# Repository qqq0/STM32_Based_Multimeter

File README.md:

# **STM32 BLE Multimeter**

**Multimeter features:**
- USB rechargeable LiPo battery  
- BLE control and data streaming  
- Auto range detection  
- Optional OLED display/button control  

**Measurement types:**
- DC voltage: 0 - 60V  
- DC current: 0 - 10A (5 sec)  
- DC power: 0 - 600 W (5 sec)  
- Resistance: 1 - 1M ohm  
- Inductance  
- Capacitance (non-polarized)  
- Diode: 3.3V  

**PCB FRONT:**

**PCB BACK:**

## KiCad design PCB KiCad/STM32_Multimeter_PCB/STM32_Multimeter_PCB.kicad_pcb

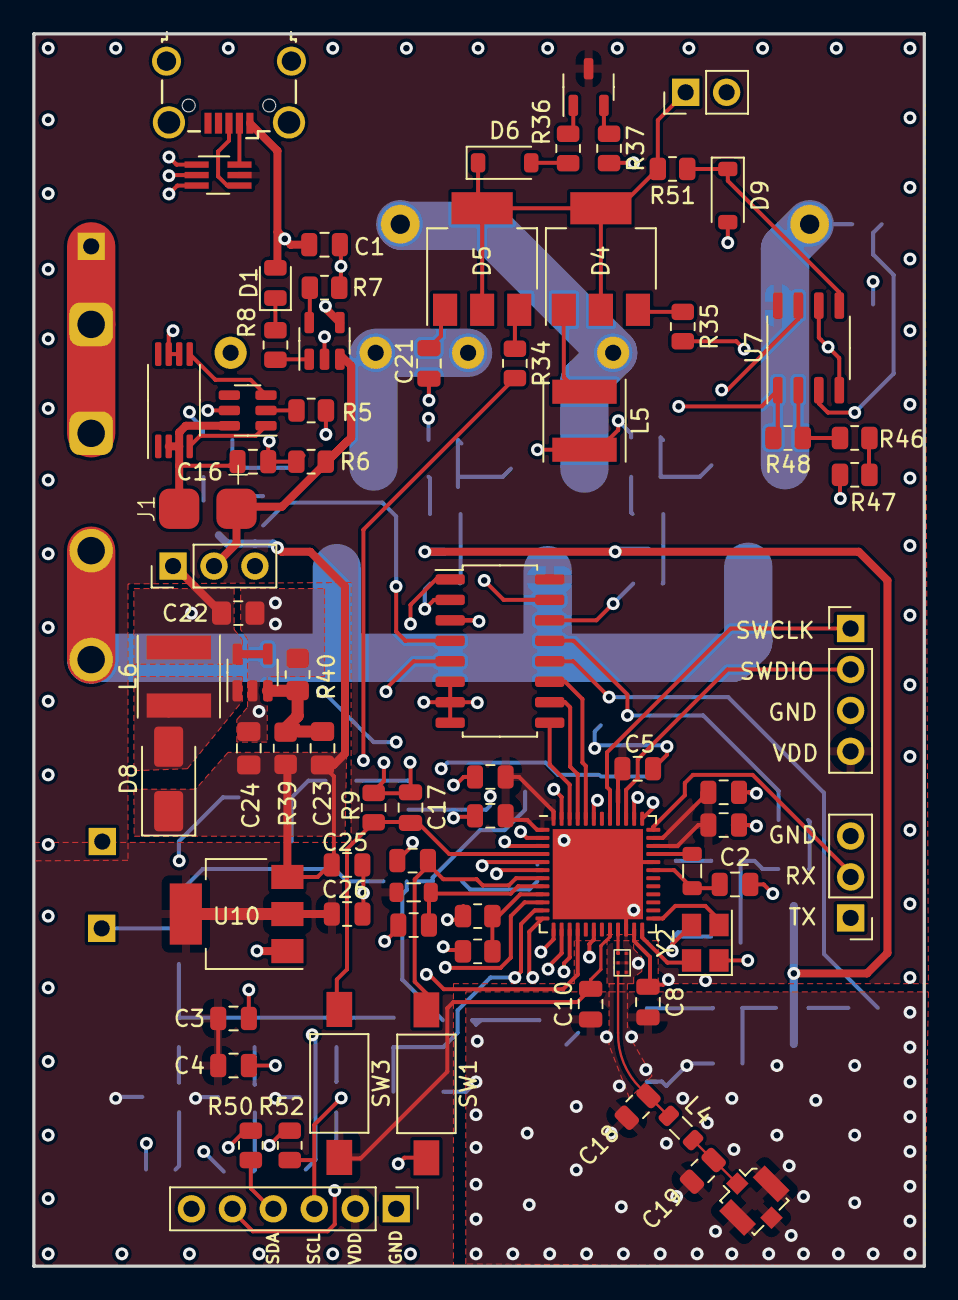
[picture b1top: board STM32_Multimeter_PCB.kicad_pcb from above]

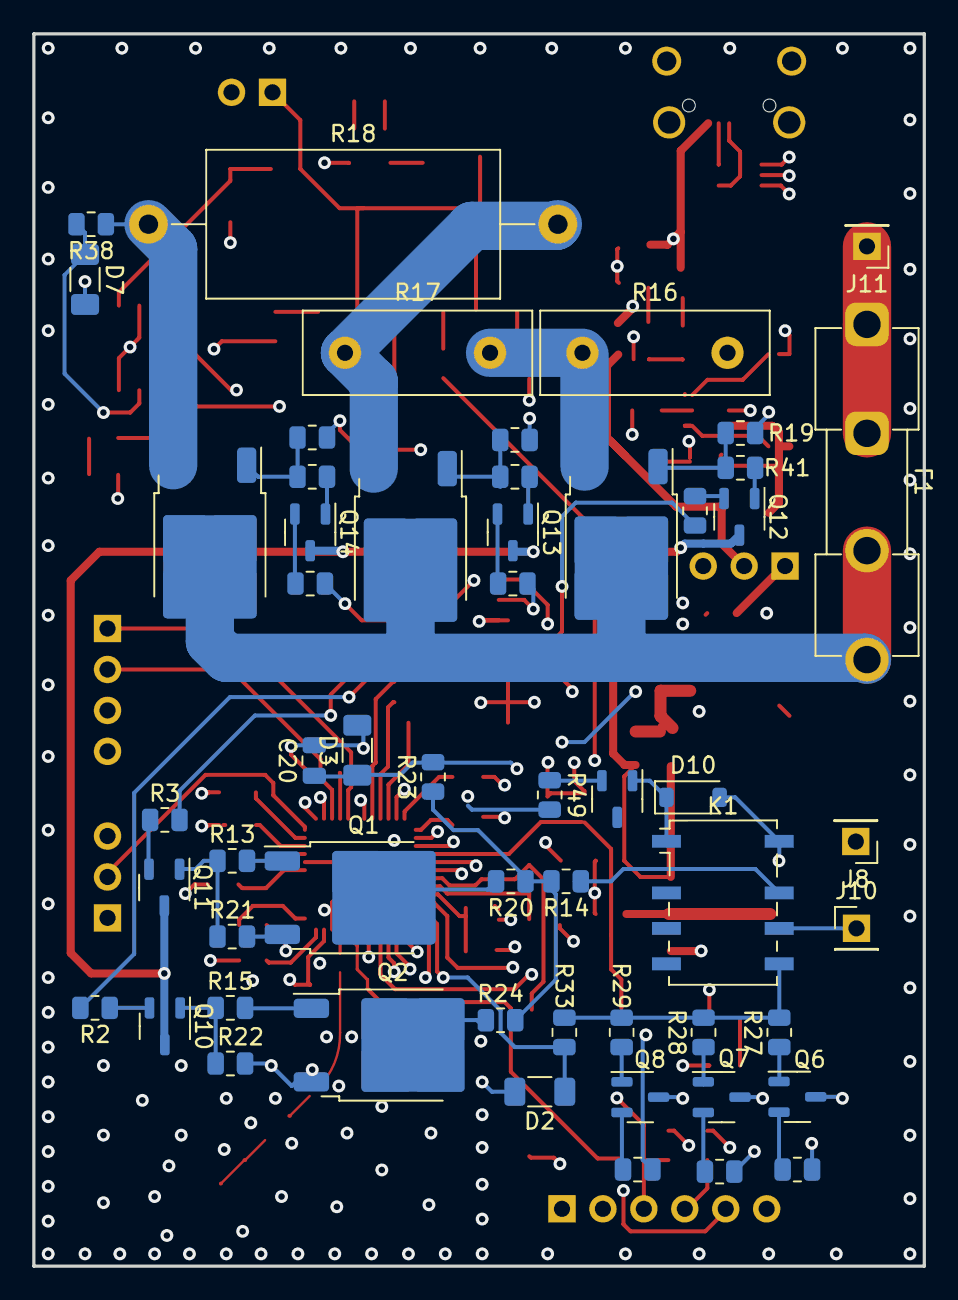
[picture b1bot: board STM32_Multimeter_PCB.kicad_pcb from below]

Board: 4 copper layers, 55.2 x 76.5 mm, 130 parts (55 on the bottom side), 105 nets.

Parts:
C1, C2, C3, C4, C11: 4,7 uF; C_0805_2012Metric
C5, C6, C7, C8, C9, C10, C12, C13, C16, C17, C20: 100 nF; C_0805_2012Metric
C18, C19: NF; C_0805_2012Metric
C21: 1uF; C_0805_2012Metric
C22, C24: 4.7uF; C_0805_2012Metric_Pad1.18x1.45mm_HandSolder
C23: 22pF; C_0805_2012Metric_Pad1.18x1.45mm_HandSolder
C25, C26: 10 uF; C_0805_2012Metric
D1: LED; LED_0805_2012Metric
D2, D3, D7: 3V3 D_Zener; R_1206_3216Metric_Pad1.30x1.75mm_HandSolder
D4, D5: Z0103MN; SOT-223
D6, D9, D10: 1N4148W; D_SOD-123
D8: 1N4001; D_SMA
F1: 10A Fuse; Fuseholder_Clip-5x20mm_Eaton_1A5601-01_Inline_P20.80x6.76mm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
J1: Conn_01x02_Pin; batt
J2: USB_B_Micro; USB_Micro-B_Wuerth_629105150521_CircularHoles
J3: Conn_01x04_Pin; PinHeader_1x04_P2.54mm_Vertical
J4: Conn_Coaxial; U.FL_Molex_MCRF_73412-0110_Vertical
J5: Conn_01x03_Pin; PinHeader_1x03_P2.54mm_Vertical
J7: Conn_01x02_Pin; PinHeader_1x02_P2.54mm_Vertical
J8, J10, J11: Conn_01x01_Pin; PinHeader_1x01_P2.54mm_Vertical
J9: Conn_01x06_Pin; PinHeader_1x06_P2.54mm_Vertical
K1: G6K-2; Relay_DPDT_Omron_G6K-2F-Y
L1, L2: 10 uH; L_0805_2012Metric
L4: 0H; L_0805_2012Metric
L5, L6: 10uH; L_Taiyo-Yuden_NR-50xx
Q1, Q2, Q3, Q4, Q5: AOD2810; TO-252-1
Q6, Q7, Q8, Q9, Q10, Q11, Q12, Q13, Q14, Q15: BC327; SOT-23-3
R2, R3, R4, R30, R31, R32, R34, R35, R37, R43, R45, R49: 2k2 R; R_0805_2012Metric
R5, R8, R13, R15, R28, R41, R42, R44: 1k R; R_0805_2012Metric
R6: 100R; R_0805_2012Metric
R7, R9, R50, R52: 2k R; R_0805_2012Metric
R11, R12: 511k R; R_0805_2012Metric
R14: 910k R; R_0805_2012Metric
R16: 0,01 R; R_Box_L14.0mm_W5.0mm_P9.00mm
R17: 0,1 R; R_Box_L14.0mm_W5.0mm_P9.00mm
R18: 1 R; R_Axial_DIN0918_L18.0mm_D9.0mm_P25.40mm_Horizontal
R19, R20, R21, R22, R23, R25, R26, R29, R33, R38, R51: 100k R; R_0805_2012Metric
R24: 9,1k R; R_0805_2012Metric
R27: 100 R; R_0805_2012Metric
R36: 220 R; R_0805_2012Metric
R39: 470k R; R_0805_2012Metric_Pad1.20x1.40mm_HandSolder
R40: 75k R; R_0805_2012Metric_Pad1.20x1.40mm_HandSolder
R46: 43k R; R_0805_2012Metric
R47: 330 R; R_0805_2012Metric
R48: 390k R; R_0805_2012Metric
SW1: NRST; SW_SPST_FSMSM
SW3: BOOT; SW_SPST_FSMSM
SW4: SW_DPDT_x2; PinHeader_1x03_P2.54mm_Vertical
U1: STM32WB55CGUx; QFN-48-1EP_7x7mm_P0.5mm_EP5.6x5.6mm
U3: LTC4054XES5-4.2; TSOT-23-5
U4: DW01A; SOT-23-6
U5: FS8205A; TSSOP-8_4.4x3mm_P0.65mm
U6: SOT-363_SC-70-6_Handsoldering
U7: SOP-8_3.9x4.9mm_P1.27mm
U8: MLPF-WB55
U9: TPS61040DBV; SOT-23-5
U10: AMS1117-3.3; SOT-223-3_TabPin2
U11: 4051; SOP-16_4.4x10.4mm_P1.27mm
Y2: Crystal_GND24; Crystal_SMD_3225-4Pin_3.2x2.5mm

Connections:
+5V: C1.2, D1.2 (A), J2.1 (VBUS), U3.4 (V_{CC})
+9V: C23.1, C24.1, C25.2, D8.1 (K), Q10.3 (E), Q11.3 (E), Q12.3 (E), Q13.3 (E), Q14.3 (E), R39.1, U10.3 (VI)
+BATT: C22.1, L6.1, R11.2, SW4.1 (A), U9.4 (EN), U9.5 (VIN)
A: U1.44 (PB4), U11.11 (A)
B: U1.45 (PB5), U11.10 (B)
BATT sens: R11.1, R12.2, U1.9 (PA0)
BU1: J9.6, U1.2 (PC14)
BU2: J9.5, U1.3 (PC15)
C: U1.46 (PB6), U11.9 (C)
C on: R34.2, U1.16 (PA7)
CL input: U1.14 (PA5), U7.7 (Voutb)
GND: C1.1, C2.2, C3.1, C4.1, C5.1, C6.1, C7.1, C8.2, C9.2, C10.1, C11.1, C12.1, C13.1, C17.1, C18.2, C19.2, C20.2, C21.2, C22.2, C24.2, C25.1, C26.1, D2.2 (A), D3.2 (A), D7.2 (A), D9.2 (A), D10.2 (A), J2.5 (GND), J2.6 (Shield), J3.3, J4.2 (Ext), J5.3, J7.2, J8.1, J9.1, K1.8, L5.2, Q1.3 (S), Q2.3 (S), R5.1, R7.1, R9.1, R12.1, R16.2, R19.2, R21.2, R22.2, R25.2, R26.2, R40.2, R46.1, R50.1, R52.1, SW1.2, U1.22 (VSSRF), U1.32 (VSSSMPS), U1.49 (VSS), U3.2 (GND), U5.6 (S2), U5.7 (S2), U6.2 (GND), U7.4 (Vss), U7.6 (Vinb-), U8.2 (GND_4), U8.4 (GND_3), U8.5 (GND_2), U8.6 (GND_1), U9.2 (GND), U10.1 (GND), U11.6 (Inh), U11.7 (VEE), U11.8 (VSS), Y2.1, Y2.3
L on: R35.2, U1.15 (PA6)
unnamed: D1.1 (K), R8.2
unnamed: D4.1 (A1), L5.1
unnamed: D4.2 (A2), D4.4 (A4), D5.2 (A2), D5.4 (A4), D6.1 (K), J7.1, R51.2
unnamed: D4.3 (G), R35.1
unnamed: C21.1, D5.1 (A1)
unnamed: D5.3 (G), R34.1
unnamed: D6.2 (A), R36.1
unnamed: D7.1 (K), R38.2, U7.3 (Vina+)
unnamed: D8.2 (A), L6.2, U9.1 (SW)
unnamed: D9.1 (K), R51.1, U7.5 (Vinb+)
unnamed: D10.1 (K), K1.1, Q15.1 (C)
unnamed: C16.1, J1.1, U4.6 (GND), U5.2 (S1), U5.3 (S1)
unnamed: J1.2, R6.2, SW4.2 (B), U3.3 (BAT)
unnamed: J2.3 (D+), U6.4 (D4)
unnamed: J2.2 (D-), U6.6 (D3)
unnamed: J3.1, U1.41 (PA14)
unnamed: J3.2, U1.39 (PA13)
unnamed: C19.1, J4.1 (In), L4.2
unnamed: J5.1, U1.18 (PA9)
unnamed: J5.2, U1.36 (PA10)
unnamed: J9.3, R52.2, U1.5 (PB8)
unnamed: J9.4, R50.2, U1.6 (PB9)
unnamed: J10.1, K1.6
unnamed: F1.1, J11.1
unnamed: K1.5, R27.2, R28.2, R29.2, R33.1
unnamed: K1.7, R14.1
unnamed: Q1.1 (D), R20.2
unnamed: Q1.2 (G), R13.2
unnamed: Q2.1 (D), R24.1
unnamed: Q2.2 (G), R15.2
unnamed: F1.2, Q3.1 (D), Q4.1 (D), Q5.1 (D)
unnamed: Q3.2 (G), R19.1, R41.1
unnamed: Q3.3 (S), R16.1, R17.2
unnamed: Q4.2 (G), R25.1, R42.1
unnamed: Q4.3 (S), R17.1, R18.2
unnamed: Q5.2 (G), R26.1, R44.1
unnamed: Q5.3 (S), R18.1, R38.1
unnamed: Q6.2 (B), R30.2
unnamed: Q6.1 (C), R27.1
unnamed: Q7.2 (B), R31.2
unnamed: Q7.1 (C), R28.1
unnamed: Q8.2 (B), R32.2
unnamed: Q8.1 (C), R29.1
unnamed: Q9.2 (B), R37.1
unnamed: Q9.1 (C), R36.2
unnamed: Q10.2 (B), R2.1
unnamed: Q10.1 (C), R15.1, R22.1
unnamed: Q11.2 (B), R3.1
unnamed: Q11.1 (C), R13.1, R21.1
unnamed: Q12.2 (B), R4.1
unnamed: Q12.1 (C), R41.2
unnamed: Q13.2 (B), R43.1
unnamed: Q13.1 (C), R42.2
unnamed: Q14.2 (B), R45.1
unnamed: Q14.1 (C), R44.2
unnamed: Q15.2 (B), R49.1
unnamed: R14.2, R20.1, R23.1, R24.2
unnamed: R46.2, R47.1
unnamed: C12.2, SW1.1, U1.7 (NRST)
unnamed: U1.25 (OSC_IN), Y2.2
unnamed: U1.24 (OSC_OUT), Y2.4
unnamed: U1.37 (PA11), U6.3 (D2)
unnamed: U1.38 (PA12), U6.1 (D1)
unnamed: U1.47 (PB7), U11.3 (X)
unnamed: C17.2, R9.2, SW3.1, U1.4 (PH3)
unnamed: U1.21 (RF1), U8.3 (IN)
unnamed: C11.2, L2.1, U1.8 (VDDA)
unnamed: C2.1, L1.2, U1.31 (VFBSMPS)
unnamed: L1.1, U1.33 (VLXSMPS)
unnamed: R7.2, U3.5 (PROG)
unnamed: R8.1, U3.1 (~CHRG)
unnamed: R5.2, U4.2 (CS)
unnamed: U4.3 (OC), U5.5 (G2)
unnamed: U4.1 (OD), U5.4 (G1)
unnamed: C16.2, R6.1, U4.5 (VCC)
unnamed: R47.2, R48.1, U7.2 (Vina-)
unnamed: C18.1, L4.1, U8.1 (OUT)
unnamed: C23.2, R39.2, R40.1, U9.3 (FB)
R input: D2.1 (K), R33.2, U1.11 (PA2)
Range 0,1A: R45.2, U11.14 (X1)
Range 1 to 100 ohm: R30.1, U11.15 (X2)
Range 1A: R43.2, U11.2 (X6)
Range 1/10: R3.2, U11.13 (X0)
Range 1/100: R2.2, U11.12 (X3)
Range 10A: R4.2, U11.4 (X7)
Range 10k to 1kk ohm: R32.1, U11.1 (X4)
Range 100 to 10k ohm: R31.1, U11.5 (X5)
Resistance rel: R49.2, U1.43 (PB3)
VDD: C3.2, C4.2, C5.2, C6.2, C7.2, C8.1, C9.1, C10.2, C13.2, C26.2, J3.4, J9.2, L2.2, Q6.3 (E), Q7.3 (E), Q8.3 (E), Q9.3 (E), SW3.2, U1.1 (VBAT), U1.20 (VDD), U1.23 (VDDRF), U1.34 (VDDSMPS), U1.35 (VDD), U1.40 (VDDUSB), U1.48 (VDD), U6.5 (VCC), U7.8 (Vdd), U10.2 (VO), U11.16 (VDD)
charge LC: R37.2, U1.13 (PA4)
current input: R48.2, U1.12 (PA3), U7.1 (Vouta)
voltage input: C20.1, D3.1 (K), R23.2, U1.10 (PA1)

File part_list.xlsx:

# | Reference | Qty | Value | Shop link | Footprint | order Qty | Price PLN | Total Price | shiping | Kolumna1
1 | C1, C2, C3, C4, C11, C22, C24 | 7 | 4,7 uF | mam 12 https://pl.aliexpress.com/item/1005006285113165.html?spm=a2g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 | Capacitor_SMD:C_0805_2012Metric | 1 | 1.69 | 6.77 | 5.08
2 | C5, C6, C7, C8, C9, C10, C12, C13, C16, C17, C20 | 11 | 100 nF | mam 6 == | Capacitor_SMD:C_0805_2012Metric | 1 | 2.1 | 2.1 | 0
3 | C18, C19 | 2 | NF |  | Capacitor_SMD:C_0805_2012Metric | 0 |  | 0
4 | C21 | 1 | 1uF |  | Capacitor_SMD:C_0805_2012Metric | 0 |  | 0
5 | C23 | 1 | 22pF |  | Capacitor_SMD:C_0805_2012Metric_Pad1.18x1.45mm_HandSolder | 0 |  | 0
6 | C25, C26 | 2 | 10 uF |  | Capacitor_SMD:C_0805_2012Metric | 0 |  | 0
7 | D1 | 1 | LED |  | LED_SMD:LED_0805_2012Metric | 0 |  | 0
8 | D2, D3, D7 | 3 | 3V3 D_Zener | https://pl.aliexpress.com/item/1005008305688305.html?spm=a2g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 | Resistor_SMD:R_1206_3216Metric_Pad1.30x1.75mm_HandSolder | 1 | 3.79 | 8.02 | 4.2300000000000004
9 | D4, D5 | 2 | Z0103MN | https://pl.aliexpress.com/item/1005003648689674.html?spm=a2g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 | Package_TO_SOT_SMD:SOT-223 | 1 | 2.39 | 7 | 4.6100000000000003
10 | D6, D9, D10, D8 | 4 | 1N4148W | - | Diode_SMD:D_SOD-123 | 0 |  | 0
11 | F1 | 1 | 10A Fuse | https://pl.aliexpress.com/item/1005003009277399.html?spm=a2g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 | Fuse:Fuseholder_Clip-5x20mm_Eaton_1A5601-01_Inline_P20.80x6.76mm_D1.70mm_Horizo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 | 1 | 7.6400000000000006 | 18.64 | 11
12 | J1 | 1 | Conn_01x02_Pin | Solder directly to PCB | moje_elementy:batt | 0 |  | 0
13 | J2 | 1 | USB_B_Micro | https://pl.aliexpress.com/item/1005006331276552.html?spm=a2g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 | Connector_USB:USB_Micro-B_Wuerth_629105150521_CircularHoles | 1 | 1.69 | 6.4499999999999993 | 4.76
14 | J3 | 1 | Conn_01x04_Pin |  | Connector_PinHeader_2.54mm:PinHeader_1x04_P2.54mm_Vertical | 0 |  | 0
15 | J4 | 1 | Conn_Coaxial | https://pl.aliexpress.com/item/1005005845330862.html?spm=a2g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 | Connector_Coaxial:U.FL_Molex_MCRF_73412-0110_Vertical | 1 | 1.99 | 7.62 | 5.63
16 | J5 | 1 | Conn_01x03_Pin |  | Connector_PinHeader_2.54mm:PinHeader_1x03_P2.54mm_Vertical | 0 |  | 0
17 | J7 | 1 | Conn_01x02_Pin |  | Connector_PinHeader_2.54mm:PinHeader_1x02_P2.54mm_Vertical | 0 |  | 0
18 | J8, J10, J11 | 3 | Conn_01x01_Pin |  | Connector_PinHeader_2.54mm:PinHeader_1x01_P2.54mm_Vertical | 0 |  | 0
19 | J9 | 1 | Conn_01x06_Pin |  | Connector_PinHeader_2.54mm:PinHeader_1x06_P2.54mm_Vertical | 0 |  | 0
20 | K1 | 1 | G6K-2 | https://pl.aliexpress.com/item/1005007294651555.html?spm=a2g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 | Relay_SMD:Relay_DPDT_Omron_G6K-2F-Y 3VDC | 1 | 11.13 | 17.060000000000002 | 5.93
21 | L1,L2 | 2 | 10 uH | https://pl.aliexpress.com/item/32955754327.html?spm=a2g0o.pr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 | Inductor_SMD:L_0805_2012Metric | 1 | 2.35 | 7.3900000000000006 | 5.04
22
23 | L4 | 1 | 0H | set | Inductor_SMD:L_0805_2012Metric | 0 |  | 0
24 | L5, L6 | 2 | 10uH | https://pl.aliexpress.com/item/1005002090028747.html?spm=a2g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 | Inductor_SMD:L_Taiyo-Yuden_NR-50xx | 1 | 2.13 | 6.95 | 4.82
25 | Q1, Q2, Q3, Q4, Q5 | 5 | AOD2810 | https://pl.aliexpress.com/item/1005005809146268.html?spm=a2g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 | moje_elementy:TO-252-1 | 1 | 7.01 | 11.04 | 4.03
26 | Q6, Q7, Q8, Q9, Q10, Q11, Q12, Q13, Q14, Q15 | 10 | BC327 | Zmienić na PCB coś SOT-23 | Package_TO_SOT_SMD:SOT-23-3 |  |  | 0
27 | R2, R3, R4, R30, R31, R32, R34, R35, R37, R43, R45, R49 | 12 | 2k2 R | set | Resistor_SMD:R_0805_2012Metric | 0 |  | 0
28 | R5, R8, R13, R15, R28, R41, R42, R44 | 8 | 1k R | set | Resistor_SMD:R_0805_2012Metric | 0 |  | 0
29 | R6 | 1 | 100R | set | Resistor_SMD:R_0805_2012Metric | 0 |  | 0
30 | R7, R9, R50, R52 | 4 | 2k R | set | Resistor_SMD:R_0805_2012Metric | 0 |  | 0
31 | R11, R12 | 2 | 511k R | set | Resistor_SMD:R_0805_2012Metric | 0 |  | 0
32 | R14 | 1 | 900k R | set | Resistor_SMD:R_0805_2012Metric | 0 |  | 0
33 | R16 | 1 | 0,01 R | https://pl.aliexpress.com/item/1005005181109774.html?spm=a2g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 | Resistor_THT:R_Box_L14.0mm_W5.0mm_P9.00mm | 1 | 1.99 | 6.8100000000000005 | 4.82
34 | R17 | 1 | 0,1 R | https://pl.aliexpress.com/item/1005005181109774.html?spm=a2g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 | Resistor_THT:R_Box_L14.0mm_W5.0mm_P9.00mm | 1 | 1.99 | 1.99
35 | R18 | 1 | 1 R |  | Resistor_THT:R_Axial_DIN0918_L18.0mm_D9.0mm_P25.40mm_Horizontal | 0 |  | 0
36 | R19, R20, R21, R22, R23, R25, R26, R29, R33, R38, R51 | 11 | 100k R | https://pl.aliexpress.com/item/1005007636030489.html?spm=a2g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 | Resistor_SMD:R_0805_2012Metric | 1 | 13.19 | 13.19 |  | 80value 2000 pcs
37 | R24 | 1 | 9,1k R | set | Resistor_SMD:R_0805_2012Metric | 0 |  | 0
38 | R27 | 1 | 100 R | set | Resistor_SMD:R_0805_2012Metric | 0 |  | 0
39 | R36 | 1 | 220 R | set | Resistor_SMD:R_0805_2012Metric | 0 |  | 0
40 | R39 | 1 | 470k R | set | Resistor_SMD:R_0805_2012Metric_Pad1.20x1.40mm_HandSolder | 0 |  | 0
41 | R40 | 1 | 75k R | set | Resistor_SMD:R_0805_2012Metric_Pad1.20x1.40mm_HandSolder | 0 |  | 0
42 | R46 | 1 | 43k R | set | Resistor_SMD:R_0805_2012Metric | 0 |  | 0
43 | R47 | 1 | 330 R | set | Resistor_SMD:R_0805_2012Metric | 0 |  | 0
44 | R48 | 1 | 390k R | set | Resistor_SMD:R_0805_2012Metric | 0 |  | 0
45 | SW1 | 1 | NRST |  | Button_Switch_SMD:SW_SPST_FSMSM | 0 |  | 0
46 | SW3 | 1 | BOOT |  | Button_Switch_SMD:SW_SPST_FSMSM | 0 |  | 0
47 | SW4 | 1 | SW_DPDT_x2 |  | Connector_PinHeader_2.54mm:PinHeader_1x03_P2.54mm_Vertical | 0 |  | 0
48 | U1 | 1 | STM32WB55CGUx | https://pl.aliexpress.com/item/1005008038998896.html?spm=a2g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 | Package_DFN_QFN:QFN-48-1EP_7x7mm_P0.5mm_EP5.6x5.6mm | 2 | 13.59 | 31.71 | 4.53
49 | U3 | 1 | LTC4054XES5-4.2 | https://pl.aliexpress.com/item/1005006928245080.html?spm=a2g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 | Package_TO_SOT_SMD:TSOT-23-5 | 1 | 2.17 | 6.74 | 4.57
50 | U4 | 1 | DW01A | https://pl.aliexpress.com/item/1005007467171055.html?spm=a2g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 | Package_TO_SOT_SMD:SOT-23-6 | 1 | 4.79 | 9.32 | 4.53
51 | U5 | 1 | FS8205A | set | Package_SO:TSSOP-8_4.4x3mm_P0.65mm | 0 |  | 0
52 | U6 | 1 | ~ | https://pl.aliexpress.com/item/1005007978414767.html?spm=a2g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 | Package_TO_SOT_SMD:SOT-363_SC-70-6_Handsoldering | 1 | 2.25 | 6.32 | 4.07
53 | U7 | 1 | MCP602 | https://pl.aliexpress.com/item/1005006922903852.html?spm=a2g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 | Package_SO:SOP-8_3.9x4.9mm_P1.27mm | 1 | 4.2 | 4.2 | 0
54 | U8 | 1 | ~ | https://pl.aliexpress.com/item/1005006779802761.html?spm=a2g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 | moje_elementy:MLPF-WB55 | 2 | 4.6900000000000004 | 13.080000000000002 | 3.7
55 | U9 | 1 | TPS61040DBV |  | Package_TO_SOT_SMD:SOT-23-5 | 0 |  | 0
56 | U10 | 1 | AMS1117-3.3 |  | Package_TO_SOT_SMD:SOT-223-3_TabPin2 | 0 |  | 0
57 | U11 | 1 | 4051 | https://pl.aliexpress.com/item/1005007329677951.html?spm=a2g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 | Package_SO:SOP-16_4.4x10.4mm_P1.27mm | 1 | 3.2 | 6.79 | 3.59
58 | Y1 | 1 | Crystal 32 MHz | https://pl.aliexpress.com/item/1005006142975427.html?spm=a2g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 | Crystal:Crystal_SMD_5032-2Pin_5.0x3.2mm_HandSoldering | 1 | 4.2 | 4.2
59 |  | 1 | Antena | https://pl.aliexpress.com/item/1005006057629673.html?spm=a2g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 | 2.4G Bluetooth wifi mała antena 5G 5.8G UFL | 1 | 6.69 | 6.69 | 0
60 |  |  |  |  |  |  |  | 0
61 |  |  |  |  |  |  |  | 0
 |  |  |  |  |  | suma | 210.07999999999996

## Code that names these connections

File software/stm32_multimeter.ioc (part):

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Mcu.Name=STM32WB55CGUx
Mcu.Package=UFQFPN48
Mcu.UserName=STM32WB55CGUx
PA0.GPIOParameters=GPIO_Label
PA0.GPIO_Label=BATT sens
PA0.Signal=ADCx_IN5
PA1.GPIOParameters=GPIO_Label
PA1.GPIO_Label=V
PA1.Signal=ADCx_IN6
PA10.Mode=Asynchronous
PA10.Signal=USART1_RX
PA11.Mode=Device
PA11.Signal=USB_DM
PA12.Mode=Device
PA12.Signal=USB_DP
PA13.Mode=Serial_Wire
PA13.Signal=SYS_JTMS-SWDIO
PA14.Mode=Serial_Wire
PA14.Signal=SYS_JTCK-SWCLK
PA2.GPIOParameters=GPIO_Label
PA2.GPIO_Label=R
PA2.Signal=ADCx_IN7
PA3.GPIOParameters=GPIO_Label
PA3.GPIO_Label=I
PA3.Signal=ADCx_IN8
PA4.GPIOParameters=GPIO_Label
PA4.GPIO_Label=charge LC
PA4.Signal=GPIO_Output
PA5.Signal=S_TIM2_CH1
PA6.GPIOParameters=GPIO_Label
PA6.GPIO_Label=L on
PA6.Signal=GPIO_Output
PA7.GPIOParameters=GPIO_Label
PA7.GPIO_Label=C on
PA7.Signal=GPIO_Output
PA9.Mode=Asynchronous
PA9.Signal=USART1_TX
PB3.GPIOParameters=GPIO_Label
PB3.GPIO_Label=Relay
PB3.Signal=GPIO_Output
PB4.GPIOParameters=GPIO_Label
PB4.GPIO_Label=A
PB4.Signal=GPIO_Output
PB5.GPIOParameters=GPIO_Label
PB5.GPIO_Label=B
PB5.Signal=GPIO_Output
PB6.GPIOParameters=GPIO_Label
PB6.GPIO_Label=C
PB6.Signal=GPIO_Output
PB7.GPIOParameters=GPIO_Label
PB7.GPIO_Label=X
PB7.Signal=GPIO_Output
PB8.Mode=I2C
PB8.Signal=I2C1_SCL
PB9.Mode=I2C
PB9.Signal=I2C1_SDA
PC14-OSC32_IN.GPIOParameters=GPIO_PuPd,GPIO_Label
PC14-OSC32_IN.GPIO_Label=BU1
PC14-OSC32_IN.GPIO_PuPd=GPIO_PULLDOWN
PC14-OSC32_IN.Signal=GPXTI14
PC15-OSC32_OUT.GPIOParameters=GPIO_PuPd,GPIO_Label
PC15-OSC32_OUT.GPIO_Label=BU2
PC15-OSC32_OUT.GPIO_PuPd=GPIO_PULLDOWN
PC15-OSC32_OUT.Signal=GPXTI15
RCC.HSE_VALUE=32000000
RCC.SYSCLKFreq_VALUE=64000000
RCC.SYSCLKSource=RCC_SYSCLKSOURCE_PLLCLK
board=custom

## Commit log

2024-11-14 Created KiCAD project
2024-11-15 Added stm32 to PCB with components nesesery for runing it
2024-11-15 Added battery charger/protection, 3,3v buck/boost regualtor andUSB connector
2024-11-16 Added mcu connectivity: SWD, USB, UART and BLE with supporting circuitry
2024-11-17 Added voltage and current sensing input
2024-11-19 Added resistance measurement circuitry
2024-11-25 Changed RF filter
2024-11-27 Added LC osicilator for inductance and capacitance measurment
2024-11-29 Added 9V SMPS, swiched 3,3V SMPS to linnear regulator
2024-11-29 Added BJT for swiching range mosfets from 9V
2024-11-29 Added shunt voltage amplifier
2024-12-03 added resistance/voltage measurment relay
2024-12-03 Added component footprints
2024-12-04 Connected measuring circuitry to STM32
2024-12-08 Created pcb schematic
2024-12-22 Routed Analog and Microcontroler section
2024-12-23 routed out signals and power planes
2024-12-25 added stiching via-s and impedance controled traces for RF
2024-12-25 created CubeIDE project, setup STM32 pins
2024-12-26 added i2c for oled and 2 buttons to pcb
2024-12-26 added pin names to silkscreen
2024-12-28 added MUX and I,R,V autorange measurment logic
2024-12-29 added TIM2 input capture for measuring frequency of the LC circuit
2025-01-02 added PCB 3D model img files
2025-01-02 added L and C measurment logic
2025-01-02 added masurment controll state machine and button interrupts
2025-01-12 added missing shop links to the part list
